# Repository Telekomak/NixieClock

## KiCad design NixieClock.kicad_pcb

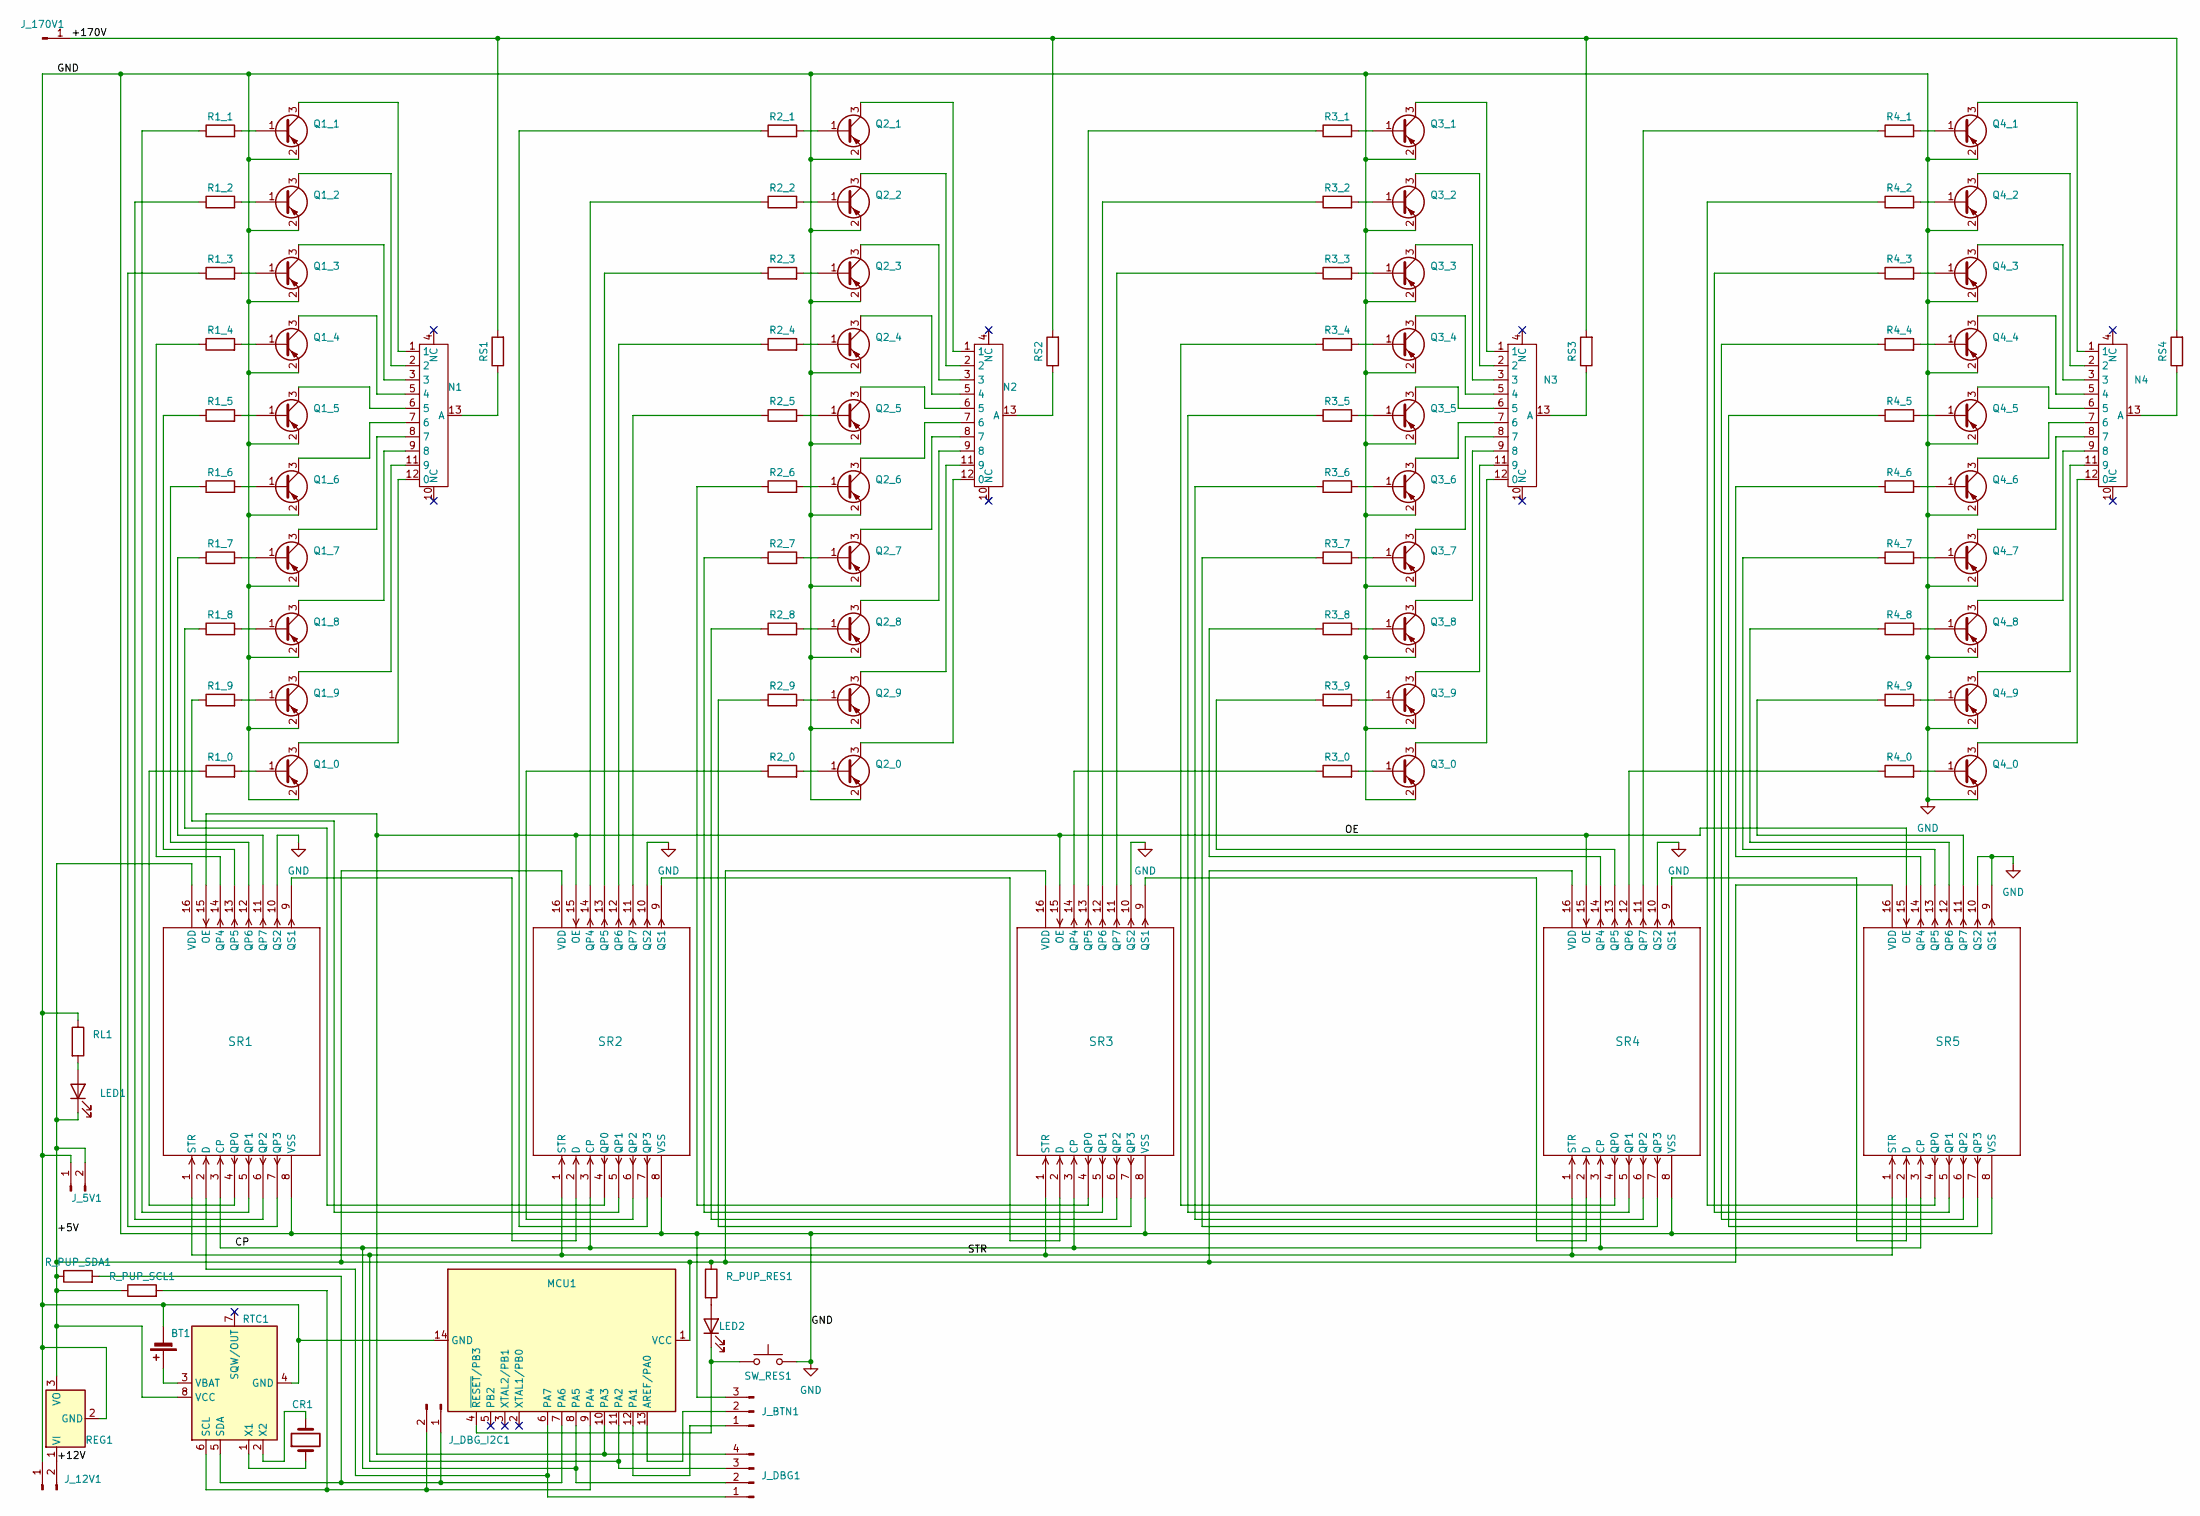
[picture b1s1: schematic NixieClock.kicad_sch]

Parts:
BT1: CR2032; CR20_holder
CR1: 32,768KHz; XTAL_AB38T-32.768KHZ
J_5V1, J_12V1: Conn_01x02_Pin; PinHeader_1x02_P2.54mm_Vertical
J_170V1: Conn_01x01_Pin; PinHeader_1x01_P2.54mm_Vertical
J_BTN1: Conn_01x03_Pin; PinHeader_1x03_P2.54mm_Vertical
J_DBG1: Conn_01x04_Pin; PinHeader_1x04_P2.54mm_Vertical
J_DBG_I2C1: Conn_01x02_Pin; PinHeader_1x02_P2.54mm_Vertical
LED1, LED2: LED; LED_1206_3216Metric_Pad1.42x1.75mm_HandSolder
MCU1: ATtiny24A-SS; SOIC-14_3.9x8.7mm_P1.27mm
N1, N2, N3, N4: Z570M
Q1_0, Q1_1, Q1_2, Q1_3, Q1_4, Q1_5, Q1_6, Q1_7, Q1_8, Q1_9, Q2_0, Q2_1, Q2_2, Q2_3, Q2_4, Q2_5, Q2_6, Q2_7, Q2_8, Q2_9, Q3_0, Q3_1, Q3_2, Q3_3, Q3_4, Q3_5, Q3_6, Q3_7, Q3_8, Q3_9, Q4_0, Q4_1, Q4_2, Q4_3, Q4_4, Q4_5, Q4_6, Q4_7, Q4_8, Q4_9: BC807; SOT-23_Handsoldering
R1_0, R1_1, R1_2, R1_3, R1_4, R1_5, R1_6, R1_7, R1_8, R1_9, R2_0, R2_1, R2_2, R2_3, R2_4, R2_5, R2_6, R2_7, R2_8, R2_9, R3_0, R3_1, R3_2, R3_3, R3_4, R3_5, R3_6, R3_7, R3_8, R3_9, R4_0, R4_1, R4_2, R4_3, R4_4, R4_5, R4_6, R4_7, R4_8, R4_9: 5K1; R_1206_3216Metric_Pad1.30x1.75mm_HandSolder
REG1: LF50CDT-TR; TO-252-2
RL1: 200; R_1206_3216Metric_Pad1.30x1.75mm_HandSolder
RS1, RS2, RS3, RS4: 82K; R_1206_3216Metric_Pad1.30x1.75mm_HandSolder
RTC1: DS1307+; DIP-8_W7.62mm_SMDSocket_SmallPads
R_PUP_RES1: 200; R_1206_3216Metric_Pad1.30x1.75mm_HandSolder
R_PUP_SCL1: 5K1; R_1206_3216Metric_Pad1.30x1.75mm_HandSolder
R_PUP_SDA1: 5K1; R_1206_3216Metric_Pad1.30x1.75mm_HandSolder
SR1, SR2, SR3, SR4, SR5: HEF4094BT; SOT109-1_NXP-M
SW_RES1: SW_Push; SW_TS1107GS

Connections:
/+5V: J_5V1.2, LED1.1 (K), MCU1.1 (VCC), REG1.3 (VO), RTC1.8 (VCC), R_PUP_RES1.1, R_PUP_SCL1.1, R_PUP_SDA1.1, SR1.16 (VDD), SR2.16 (VDD), SR3.16 (VDD), SR4.16 (VDD), SR5.16 (VDD)
/+12V: J_12V1.2, REG1.1 (VI)
/+170V: J_170V1.1, RS1.2, RS2.2, RS3.2, RS4.2
/CP: J_DBG1.2, MCU1.8 (PA5), SR1.3 (CP), SR2.3 (CP), SR3.3 (CP), SR4.3 (CP), SR5.3 (CP)
/OE: J_DBG1.4, MCU1.10 (PA3), SR1.15 (OE), SR2.15 (OE), SR3.15 (OE), SR4.15 (OE), SR5.15 (OE)
/STR: J_DBG1.3, MCU1.11 (PA2), SR1.1 (STR), SR2.1 (STR), SR3.1 (STR), SR4.1 (STR), SR5.1 (STR)
GND: BT1.2 (-), J_5V1.1, J_12V1.1, J_BTN1.3, MCU1.14 (GND), Q1_0.2 (E), Q1_1.2 (E), Q1_2.2 (E), Q1_3.2 (E), Q1_4.2 (E), Q1_5.2 (E), Q1_6.2 (E), Q1_7.2 (E), Q1_8.2 (E), Q1_9.2 (E), Q2_0.2 (E), Q2_1.2 (E), Q2_2.2 (E), Q2_3.2 (E), Q2_4.2 (E), Q2_5.2 (E), Q2_6.2 (E), Q2_7.2 (E), Q2_8.2 (E), Q2_9.2 (E), Q3_0.2 (E), Q3_1.2 (E), Q3_2.2 (E), Q3_3.2 (E), Q3_4.2 (E), Q3_5.2 (E), Q3_6.2 (E), Q3_7.2 (E), Q3_8.2 (E), Q3_9.2 (E), Q4_0.2 (E), Q4_1.2 (E), Q4_2.2 (E), Q4_3.2 (E), Q4_4.2 (E), Q4_5.2 (E), Q4_6.2 (E), Q4_7.2 (E), Q4_8.2 (E), Q4_9.2 (E), REG1.2 (GND), RL1.1, RTC1.4 (GND), SR1.8 (VSS), SR1.10 (QS2), SR2.8 (VSS), SR2.10 (QS2), SR3.8 (VSS), SR3.10 (QS2), SR4.8 (VSS), SR4.10 (QS2), SR5.8 (VSS), SR5.9 (QS1), SR5.10 (QS2), SW_RES1.2
unnamed: BT1.1 (+), RTC1.3 (VBAT)
unnamed: J_BTN1.1, MCU1.12 (PA1)
unnamed: J_BTN1.2, MCU1.13 (AREF/PA0)
unnamed: J_DBG1.1, MCU1.6 (PA7), SR1.2 (D)
unnamed: J_DBG_I2C1.1, MCU1.7 (PA6), RTC1.5 (SDA), R_PUP_SDA1.2
unnamed: J_DBG_I2C1.2, MCU1.9 (PA4), RTC1.6 (SCL), R_PUP_SCL1.2
unnamed: LED1.2 (A), RL1.2
unnamed: LED2.2 (A), R_PUP_RES1.2
unnamed: LED2.1 (K), MCU1.4 (~RESET/PB3), SW_RES1.1
unnamed: N1.12 (0), Q1_0.3 (C)
unnamed: N1.5 (4), Q1_4.3 (C)
unnamed: N1.6 (5), Q1_5.3 (C)
unnamed: N1.7 (6), Q1_6.3 (C)
unnamed: N1.8 (7), Q1_7.3 (C)
unnamed: N1.9 (8), Q1_8.3 (C)
unnamed: N1.11 (9), Q1_9.3 (C)
unnamed: N1.13 (A), RS1.1
unnamed: N2.12 (0), Q2_0.3 (C)
unnamed: N2.5 (4), Q2_4.3 (C)
unnamed: N2.6 (5), Q2_5.3 (C)
unnamed: N2.7 (6), Q2_6.3 (C)
unnamed: N2.8 (7), Q2_7.3 (C)
unnamed: N2.9 (8), Q2_8.3 (C)
unnamed: N2.11 (9), Q2_9.3 (C)
unnamed: N2.13 (A), RS2.1
unnamed: N3.12 (0), Q3_0.3 (C)
unnamed: N3.5 (4), Q3_4.3 (C)
unnamed: N3.6 (5), Q3_5.3 (C)
unnamed: N3.7 (6), Q3_6.3 (C)
unnamed: N3.8 (7), Q3_7.3 (C)
unnamed: N3.9 (8), Q3_8.3 (C)
unnamed: N3.11 (9), Q3_9.3 (C)
unnamed: N3.13 (A), RS3.1
unnamed: N4.12 (0), Q4_0.3 (C)
unnamed: N4.5 (4), Q4_4.3 (C)
unnamed: N4.6 (5), Q4_5.3 (C)
unnamed: N4.7 (6), Q4_6.3 (C)
unnamed: N4.8 (7), Q4_7.3 (C)
unnamed: N4.9 (8), Q4_8.3 (C)
unnamed: N4.11 (9), Q4_9.3 (C)
unnamed: N4.13 (A), RS4.1
unnamed: Q1_0.1 (B), R1_0.2
unnamed: Q1_1.1 (B), R1_1.2
unnamed: N1.1, Q1_1.3 (C)
unnamed: Q1_2.1 (B), R1_2.2
unnamed: N1.2, Q1_2.3 (C)
unnamed: Q1_3.1 (B), R1_3.2
unnamed: N1.3, Q1_3.3 (C)
unnamed: Q1_4.1 (B), R1_4.2
unnamed: Q1_5.1 (B), R1_5.2
unnamed: Q1_6.1 (B), R1_6.2
unnamed: Q1_7.1 (B), R1_7.2
unnamed: Q1_8.1 (B), R1_8.2
unnamed: Q1_9.1 (B), R1_9.2
unnamed: Q2_0.1 (B), R2_0.2
unnamed: Q2_1.1 (B), R2_1.2
unnamed: N2.1, Q2_1.3 (C)
unnamed: Q2_2.1 (B), R2_2.2
unnamed: N2.2, Q2_2.3 (C)
unnamed: Q2_3.1 (B), R2_3.2
unnamed: N2.3, Q2_3.3 (C)
unnamed: Q2_4.1 (B), R2_4.2
unnamed: Q2_5.1 (B), R2_5.2
unnamed: Q2_6.1 (B), R2_6.2
unnamed: Q2_7.1 (B), R2_7.2
unnamed: Q2_8.1 (B), R2_8.2
unnamed: Q2_9.1 (B), R2_9.2
unnamed: Q3_0.1 (B), R3_0.2
unnamed: Q3_1.1 (B), R3_1.2
unnamed: N3.1, Q3_1.3 (C)
unnamed: Q3_2.1 (B), R3_2.2
unnamed: N3.2, Q3_2.3 (C)
unnamed: Q3_3.1 (B), R3_3.2
unnamed: N3.3, Q3_3.3 (C)
unnamed: Q3_4.1 (B), R3_4.2
unnamed: Q3_5.1 (B), R3_5.2
unnamed: Q3_6.1 (B), R3_6.2
unnamed: Q3_7.1 (B), R3_7.2
unnamed: Q3_8.1 (B), R3_8.2
unnamed: Q3_9.1 (B), R3_9.2
unnamed: Q4_0.1 (B), R4_0.2
unnamed: Q4_1.1 (B), R4_1.2
unnamed: N4.1, Q4_1.3 (C)
unnamed: Q4_2.1 (B), R4_2.2
unnamed: N4.2, Q4_2.3 (C)
unnamed: Q4_3.1 (B), R4_3.2
unnamed: N4.3, Q4_3.3 (C)
unnamed: Q4_4.1 (B), R4_4.2
unnamed: Q4_5.1 (B), R4_5.2
unnamed: Q4_6.1 (B), R4_6.2
unnamed: Q4_7.1 (B), R4_7.2
unnamed: Q4_8.1 (B), R4_8.2
unnamed: Q4_9.1 (B), R4_9.2
unnamed: CR1.1, RTC1.1 (X1)
unnamed: CR1.2, RTC1.2 (X2)
unnamed: R1_0.1, SR1.4 (QP0)
unnamed: R1_1.1, SR1.5 (QP1)
unnamed: R1_2.1, SR1.6 (QP2)
unnamed: R1_3.1, SR1.7 (QP3)
unnamed: R1_4.1, SR1.14 (QP4)
unnamed: R1_5.1, SR1.13 (QP5)
unnamed: R1_6.1, SR1.12 (QP6)
unnamed: R1_7.1, SR1.11 (QP7)
unnamed: SR1.9 (QS1), SR2.2 (D)
unnamed: R1_8.1, SR2.4 (QP0)
unnamed: R1_9.1, SR2.5 (QP1)
unnamed: R2_0.1, SR2.6 (QP2)
unnamed: R2_1.1, SR2.7 (QP3)
unnamed: R2_2.1, SR2.14 (QP4)
unnamed: R2_3.1, SR2.13 (QP5)
unnamed: R2_4.1, SR2.12 (QP6)
unnamed: R2_5.1, SR2.11 (QP7)
unnamed: SR2.9 (QS1), SR3.2 (D)
unnamed: R2_6.1, SR3.4 (QP0)
unnamed: R2_7.1, SR3.5 (QP1)
unnamed: R2_8.1, SR3.6 (QP2)
unnamed: R2_9.1, SR3.7 (QP3)
unnamed: R3_0.1, SR3.14 (QP4)
unnamed: R3_1.1, SR3.13 (QP5)
unnamed: R3_2.1, SR3.12 (QP6)
unnamed: R3_3.1, SR3.11 (QP7)
unnamed: SR3.9 (QS1), SR4.2 (D)
unnamed: R3_4.1, SR4.4 (QP0)
unnamed: R3_5.1, SR4.5 (QP1)
unnamed: R3_6.1, SR4.6 (QP2)
unnamed: R3_7.1, SR4.7 (QP3)
unnamed: R3_8.1, SR4.14 (QP4)
unnamed: R3_9.1, SR4.13 (QP5)
unnamed: R4_0.1, SR4.12 (QP6)
unnamed: R4_1.1, SR4.11 (QP7)
unnamed: SR4.9 (QS1), SR5.2 (D)
unnamed: R4_2.1, SR5.4 (QP0)
unnamed: R4_3.1, SR5.5 (QP1)
unnamed: R4_4.1, SR5.6 (QP2)
unnamed: R4_5.1, SR5.7 (QP3)
unnamed: R4_6.1, SR5.14 (QP4)
unnamed: R4_7.1, SR5.13 (QP5)
unnamed: R4_8.1, SR5.12 (QP6)
unnamed: R4_9.1, SR5.11 (QP7)

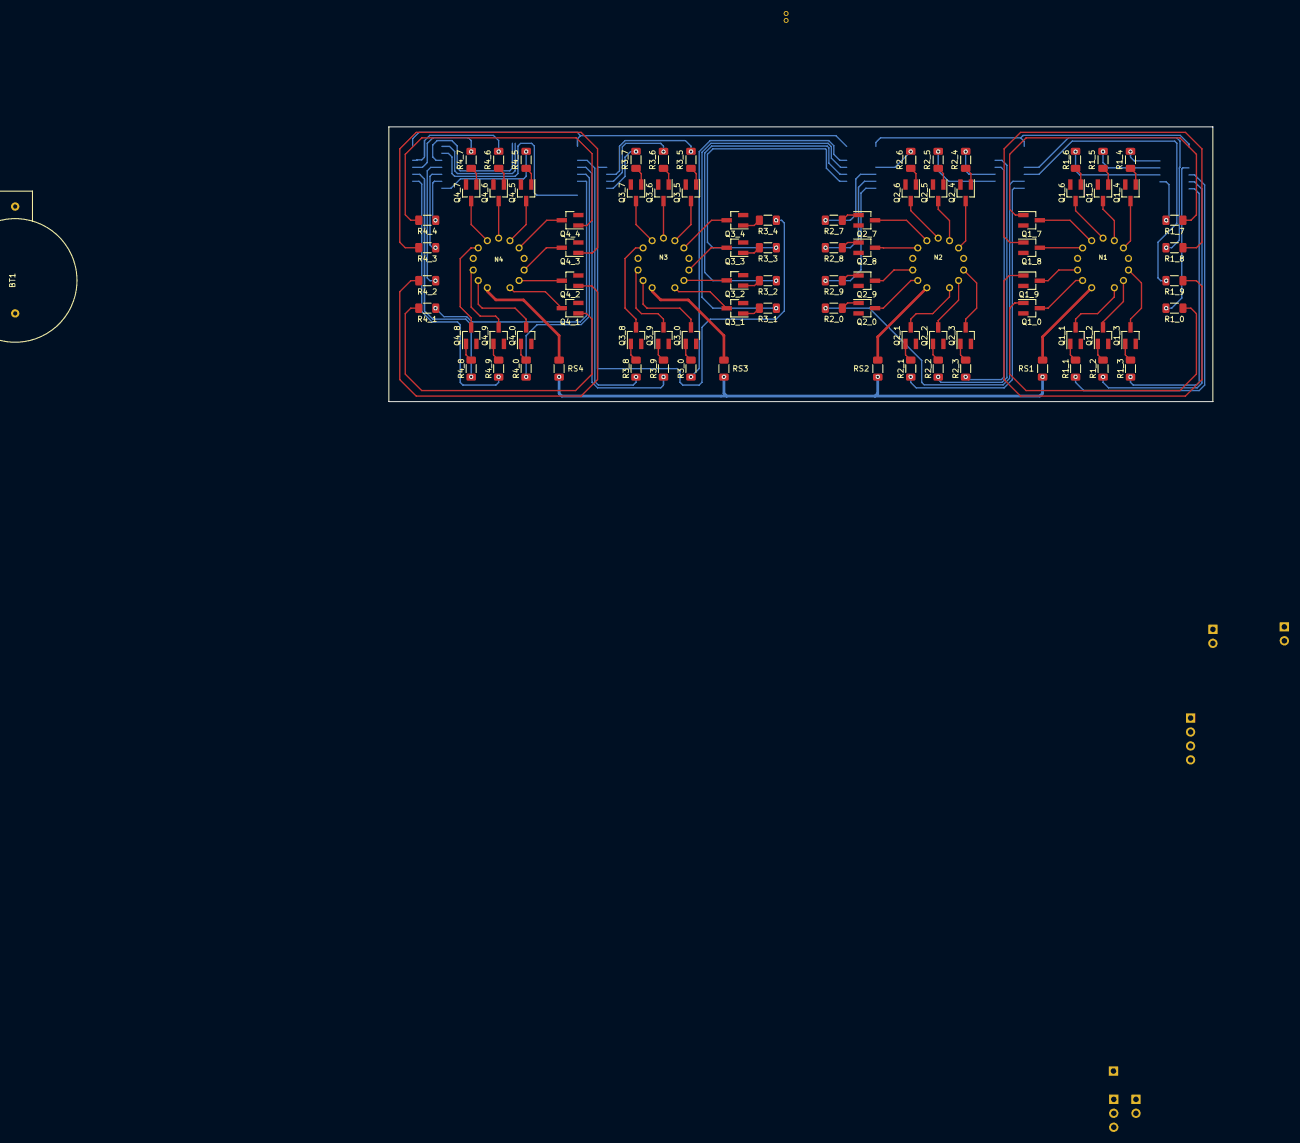
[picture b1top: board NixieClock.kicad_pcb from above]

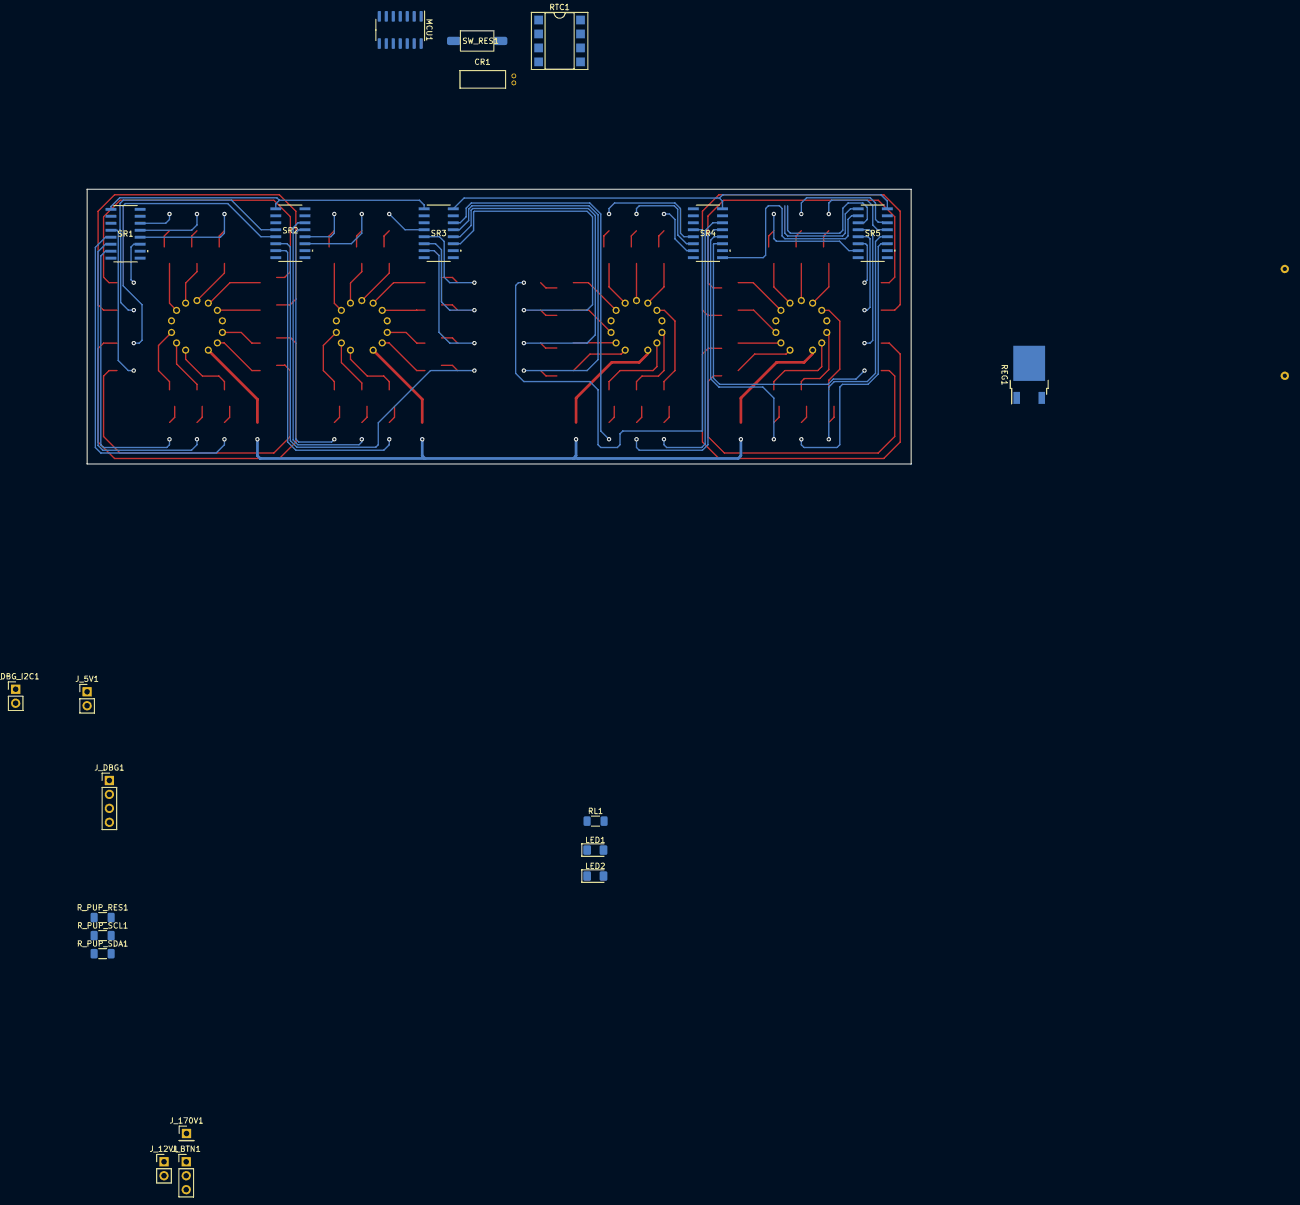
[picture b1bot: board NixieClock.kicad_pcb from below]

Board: 2 copper layers, 150.0 x 50.0 mm, 111 parts (22 on the bottom side), 146 nets.

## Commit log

2023-09-11 init
2023-09-13 added z570m symbol
2023-09-17 Created shcema
2023-09-23 updated schematic
2023-09-26 finished schematic
2023-11-19 pcb update
